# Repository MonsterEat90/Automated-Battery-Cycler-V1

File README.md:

# Automated-Battery-Cycler-V1
This device enabled you to test the endurance of your battery from LiFePO4, Li-On, and Li-Po (1 Cell). The size right now is for 18650 or 26650 battery cell. The load is an IRFZ44N with CC (Constant Current) and CP (Constant Power) mode.
This project is coded with PlatformIO.

Parts needed for this project:
1. ESP32 DevKit V1
2. INA219
3. ADS1115
4. TC4422
5. IRFZ44N
6. Voltage divider (R1 10K R2 10K) with 100nF ceramic cap for filter
7. NTC 10k and R2 10K (act like a Voltage divider) in series with 100nF cap for filter
8. Custom made 2 channel SPDT relay
9. 470uF electrolytic cap
10. 22uF electrolytic cap
11. MicroSD card module

# Schematic

It is best to drive the TC4422 with +12V for better control for the MOSFET and you can still give it PWN straight from the ESP32 pin. You can also change the relay with something more capable.
REMINDER!!!: Change the shunt in the INA219 according to how much current you need or use INA226 for better resolution.

# PCB

This is my PCB. Still quite basic but sufficient enough for this project.

Everything can be change according to your need. Let me know what your thought about this project.

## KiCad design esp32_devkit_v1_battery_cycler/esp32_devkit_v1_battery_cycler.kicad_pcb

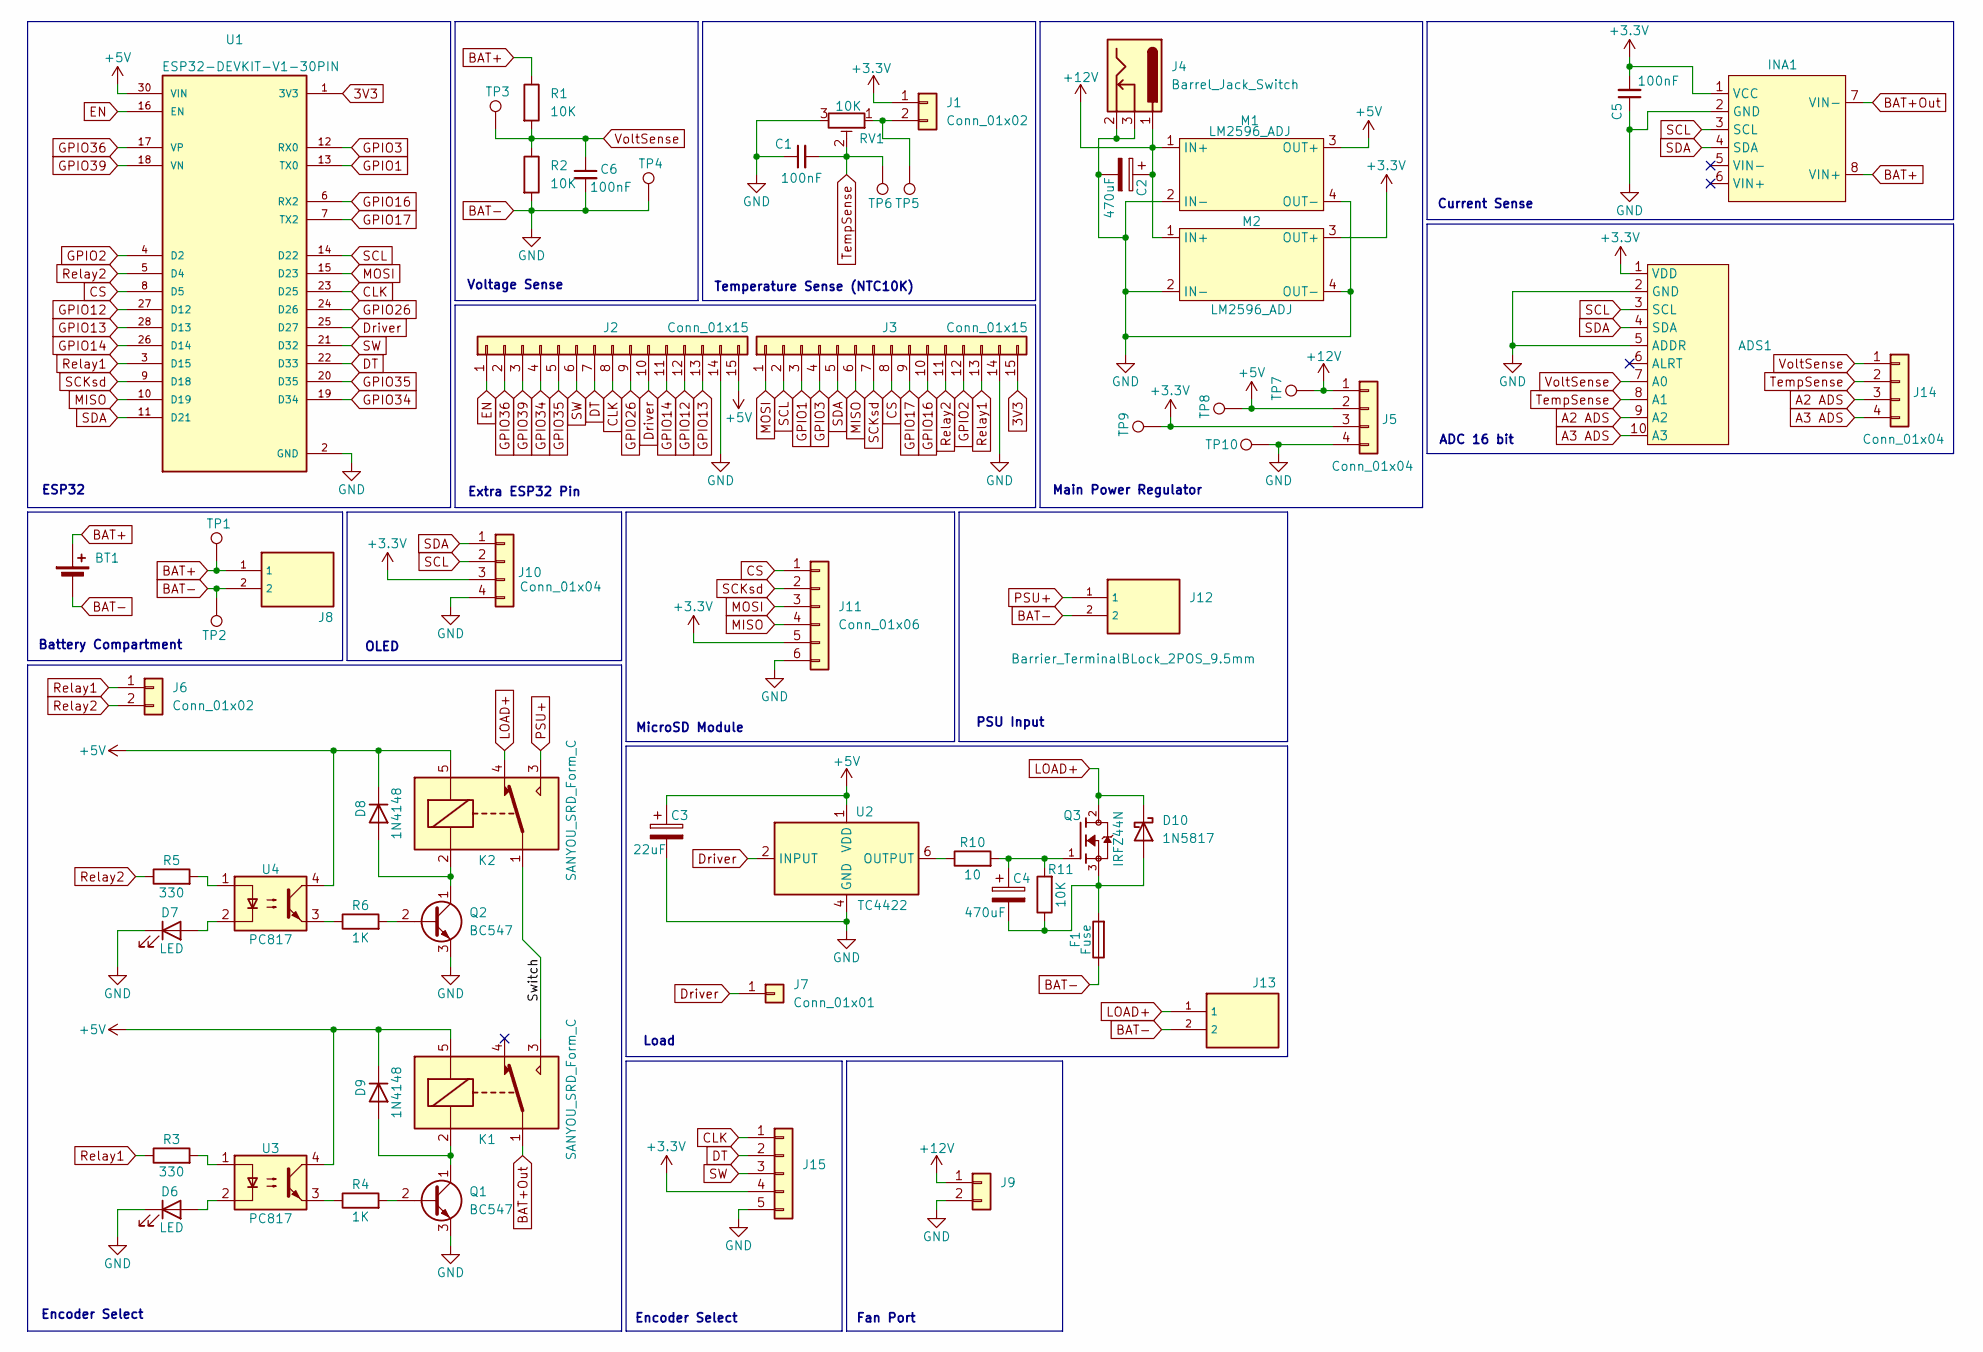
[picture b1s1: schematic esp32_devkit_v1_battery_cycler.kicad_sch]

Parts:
ADS1: ADS1115
BT1: Battery_Cell; 26650BatteryHolder_THT_RoundPin
C1, C5, C6: 100nF; C_Disc_D5.0mm_W2.5mm_P2.50mm
C2, C4: 470uF; CP_Radial_D8.0mm_P5.00mm
C3: 22uF; CP_Radial_D8.0mm_P5.00mm
D6, D7: LED; LED_D5.0mm
D8, D9: 1N4148; D_DO-35_SOD27_P7.62mm_Horizontal
D10: 1N5817; D_DO-41_SOD81_P10.16mm_Horizontal
F1: Fuse; Fuseholder_Clip-5x20mm_Eaton_1A5601-01_Inline_P20.80x6.76mm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
INA1: INA219
J1, J6, J9: Conn_01x02; PinHeader_1x02_P2.54mm_Vertical
J2, J3: Conn_01x15; PinHeader_1x15_P2.54mm_Vertical
J4: Barrel_Jack_Switch; BarrelJack_Horizontal
J5, J10, J14: Conn_01x04; PinHeader_1x04_P2.54mm_Vertical
J7: Conn_01x01; PinHeader_1x01_P2.54mm_Vertical
J8, J12, J13: Barrier_TerminalBLock_2POS_9.5mm; Barrier_Terminal_Block_2POS_HolePitch9.5mm
J11: Conn_01x06; PinHeader_1x06_P2.54mm_Vertical
J15: Conn_01x05; PinHeader_1x05_P2.54mm_Vertical
K1, K2: SANYOU_SRD_Form_C; Relay_SPDT_SANYOU_SRD_Series_Form_C
M1, M2: LM2596_ADJ; DCDC_StepDown_LM2596
Q1, Q2: BC547; TO-92_Inline
Q3: IRFZ44N; PARTREV 09/21/10
R1, R2: 10K; R_Axial_DIN0309_L9.0mm_D3.2mm_P12.70mm_Horizontal
R3, R5: 330; R_Axial_DIN0207_L6.3mm_D2.5mm_P10.16mm_Horizontal
R4, R6: 1K; R_Axial_DIN0207_L6.3mm_D2.5mm_P10.16mm_Horizontal
R10: 10; R_Axial_DIN0207_L6.3mm_D2.5mm_P10.16mm_Horizontal
R11: 10K; R_Axial_DIN0207_L6.3mm_D2.5mm_P10.16mm_Horizontal
RV1: 10K; Potentiometer_Runtron_RM-065_Vertical
TP1, TP2, TP3, TP4, TP5, TP6, TP7, TP8, TP9, TP10: TestPoint; TestPoint_Pad_D2.0mm
U1: ESP32-DEVKIT-V1-30PIN; ESP32DEVKITv1_30pin; PARTREV N/A
U2: TC4422; DIP-8_W7.62mm
U3, U4: PC817; DIP-4_W7.62mm

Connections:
3V3: J3.15, U1.1 (3V3)
+3.3V: ADS1.1 (VDD), C5.2, INA1.1 (VCC), J1.1, J5.3, J10.3, J11.5, J15.4, M2.3 (OUT+), TP9.1
+5V: C3.1, D8.1 (K), D9.1 (K), J2.15, J5.2, K1.5, K2.5, M1.3 (OUT+), TP8.1, U1.30 (VIN), U2.1 (VDD), U2.8 (VDD), U3.4, U4.4
+12V: C2.1, J4.1, J5.1, J9.1, M1.1 (IN+), M2.1 (IN+), TP7.1
/Switch: K1.3, K2.1
A2 ADS: ADS1.9 (A2), J14.3
A3 ADS: ADS1.10 (A3), J14.4
BAT+: BT1.1 (+), INA1.8 (VIN+), J8.1, R1.1, TP1.1
BAT+Out: INA1.7 (VIN-), K1.1
BAT-: ADS1.2 (GND), ADS1.5 (ADDR), BT1.2 (-), C1.1, C2.2, C3.2, C5.1, C6.2, D6.1 (K), D7.1 (K), F1.1, INA1.2 (GND), J2.14, J3.14, J4.2, J4.3, J5.4, J8.2, J9.2, J10.4, J11.6, J12.2, J13.2, J15.5, M1.2 (IN-), M1.4 (OUT-), M2.2 (IN-), M2.4 (OUT-), Q1.3 (E), Q2.3 (E), R2.2, RV1.3, TP2.1, TP4.1, TP10.1, U1.2 (GND), U1.29 (GND), U2.4 (GND), U2.5 (GND)
CLK: J2.8, J15.1, U1.23 (D25)
CS: J3.8, J11.1, U1.8 (D5)
DT: J2.7, J15.2, U1.22 (D33)
Driver: J2.10, J7.1, U1.25 (D27), U2.2 (INPUT)
EN: J2.1, U1.16 (EN)
GPIO1: J3.3, U1.13 (TX0)
GPIO2: J3.12, U1.4 (D2)
GPIO3: J3.4, U1.12 (RX0)
GPIO12: J2.12, U1.27 (D12)
GPIO13: J2.13, U1.28 (D13)
GPIO14: J2.11, U1.26 (D14)
GPIO16: J3.10, U1.6 (RX2)
GPIO17: J3.9, U1.7 (TX2)
GPIO26: J2.9, U1.24 (D26)
GPIO34: J2.4, U1.19 (D34)
GPIO35: J2.5, U1.20 (D35)
GPIO36: J2.2, U1.17 (VP)
GPIO39: J2.3, U1.18 (VN)
LOAD+: D10.1 (K), J13.1, K2.4, Q3.2
MISO: J3.6, J11.4, U1.10 (D19)
MOSI: J3.1, J11.3, U1.15 (D23)
unnamed: C4.1, Q3.1, R10.2, R11.2
unnamed: D6.2 (A), U3.2
unnamed: D7.2 (A), U4.2
unnamed: D8.2 (A), K2.2, Q2.1 (C)
unnamed: D9.2 (A), K1.2, Q1.1 (C)
unnamed: C4.2, D10.2 (A), F1.2, Q3.3, R11.1
unnamed: J1.2, RV1.1, TP5.1
unnamed: Q1.2 (B), R4.2
unnamed: Q2.2 (B), R6.2
unnamed: R3.2, U3.1
unnamed: R4.1, U3.3
unnamed: R5.2, U4.1
unnamed: R6.1, U4.3
unnamed: R10.1, U2.6 (OUTPUT), U2.7 (OUTPUT)
PSU+: J12.1, K2.3
Relay1: J3.13, J6.1, R3.1, U1.3 (D15)
Relay2: J3.11, J6.2, R5.1, U1.5 (D4)
SCKsd: J3.7, J11.2, U1.9 (D18)
SCL: ADS1.3 (SCL), INA1.3 (SCL), J3.2, J10.2, U1.14 (D22)
SDA: ADS1.4 (SDA), INA1.4 (SDA), J3.5, J10.1, U1.11 (D21)
SW: J2.6, J15.3, U1.21 (D32)
TempSense: ADS1.8 (A1), C1.2, J14.2, RV1.2, TP6.1
VoltSense: ADS1.7 (A0), C6.1, J14.1, R1.2, R2.1, TP3.1

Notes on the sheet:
Voltage Sense
OLED
ESP32
Encoder Select
Fan Port
Extra ESP32 Pin
ADC 16 bit
Current Sense
Temperature Sense (NTC10K)
Main Power Regulator
Load
PSU Input
MicroSD Module
Battery Compartment

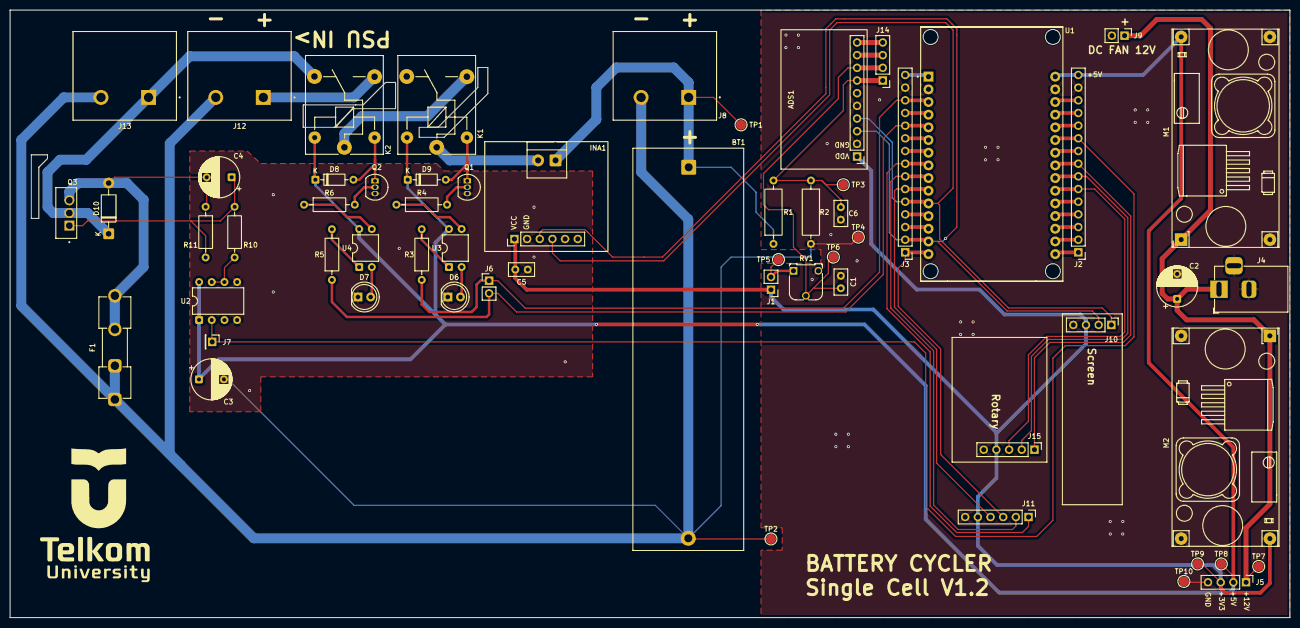
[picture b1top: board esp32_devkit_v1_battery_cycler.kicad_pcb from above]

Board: 2 copper layers, 256.5 x 121.8 mm, 60 parts (0 on the bottom side), 54 nets.
